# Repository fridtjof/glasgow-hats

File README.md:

# some HATs for the glasgow

okay there's just one so far but i've got another one i just haven't
put together yet. it's pretty simple, too.

## kicad library

in the 'kicadlib' directory, and the Releases area of github, there's
a downloadable library you can install into kicad which includes two
symbols and a footprint for making glasgow HATs. see the README in that
directory for more details.

## super breakout screw terminal hat

the name could use some work. brings the pins multiple ways, ending
in screw terminals with some holes through the PCB for optional
strain relief.

this was created when i was working on interfacing with something
through a cable i'd cut in half. i needed to bring the individual
wires into screw terminals, ideally keeping them from pulling out.
i also had to put a logic analyzer and a scope on some of the lines
to figure out what was going on. this would've been really handy.

# related content

- [my glasgow fork](https://github.com/jkominek/glasgow) has the various
  applets i've written, in it.
- [x16glasgow](https://github.com/jkominek/x16glasgow) is a HAT which adapts
  the glasgow to the Commander X16's bus as an MMIO device.

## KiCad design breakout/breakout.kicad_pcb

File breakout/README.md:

# features

Okay, per the picture:

you can work out most things.

The four rows of 0.100" header pins are intended to go female, male,
male, female, to minimize the opportunity for shorts with the female
header that the board uses to plug into the glasgow.

Speaking of which, if you used a header with very long pins for that,
you could plug the breakout cable that comes with the 1BitSquared
Glasgow into those pins, and use it, too.

The 8-pin connector is intended for looped test points, so that you
can clip oscilloscope probes on to the lines. The exposed planes along
the edges are for your probe's ground clip.

On the right there's space for screw terminals. Ground is
available twice, just in case there are two grounds in the cable
(or whatever) that you're working with, and you'd like to secure
both of them.

Finally, the little holes are for optional strain relief. You can run
your wires through them before tightening them down in the screw
terminals. Should reduce the likelihood that they'll pop out at an
awkward moment.

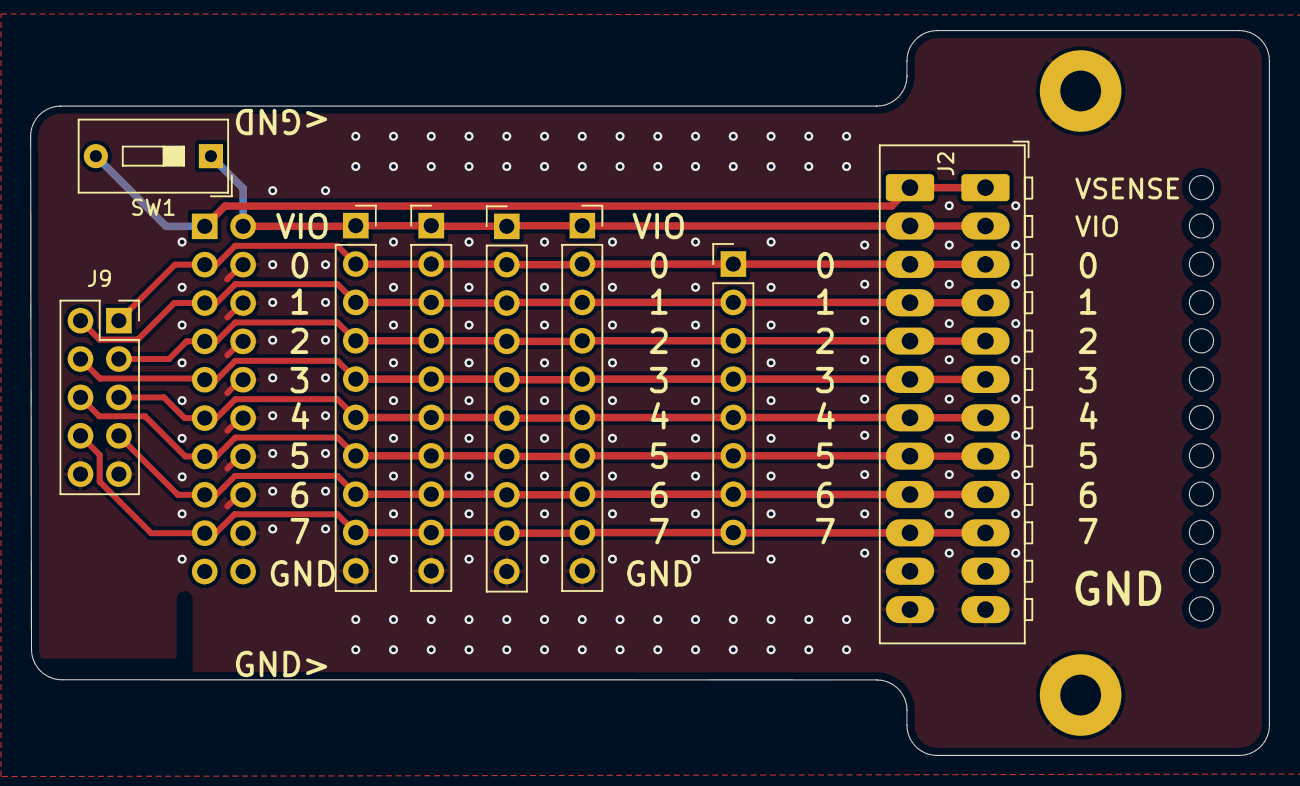
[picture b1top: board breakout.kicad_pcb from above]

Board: 2 copper layers, 82.0 x 48.0 mm, 11 parts (1 on the bottom side), 11 nets.

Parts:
H1, H2: MountingHole_Pad; MountingHole_2.7mm_M2.5_Pad
J1: Glasgow; PinSocket_2x10_P2.54mm_Vertical
J2: ScrewTerminals; TerminalBlock_not_WAGO_233-512_2x12_P2.54mm
J3, J5: SignalsMale; PinHeader_1x10_P2.54mm_Vertical
J4, J6: SignalsFemale; PinSocket_1x10_P2.54mm_Vertical
J7: TestPoints; PinHeader_1x08_P2.54mm_Vertical
J9: FX2LA; PinSocket_2x05_P2.54mm_Vertical
SW1: SW_SPST; SW_DIP_SPSTx01_Slide_9.78x4.72mm_W7.62mm_P2.54mm

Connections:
/D0: J1.3, J2.3, J3.2, J4.2, J5.2, J6.2, J7.1, J9.1
/D1: J1.5, J2.4, J3.3, J4.3, J5.3, J6.3, J7.2, J9.2
/D2: J1.7, J2.5, J3.4, J4.4, J5.4, J6.4, J7.3, J9.3
/D3: J1.9, J2.6, J3.5, J4.5, J5.5, J6.5, J7.4, J9.4
/D4: J1.11, J2.7, J3.6, J4.6, J5.6, J6.6, J7.5, J9.5
/D5: J1.13, J2.8, J3.7, J4.7, J5.7, J6.7, J7.6, J9.6
/D6: J1.15, J2.9, J3.8, J4.8, J5.8, J6.8, J7.7, J9.7
/D7: J1.17, J2.10, J3.9, J4.9, J5.9, J6.9, J7.8, J9.8
/VSENSE: J1.1, J2.1, SW1.2 (B)
GND: H1.1, H2.1, J1.4, J1.6, J1.8, J1.10, J1.12, J1.14, J1.16, J1.18, J2.11, J2.12, J3.10, J4.10, J5.10, J6.10, J9.9, J9.10
VBUS: J1.2, J2.2, J3.1, J4.1, J5.1, J6.1, SW1.1 (A)

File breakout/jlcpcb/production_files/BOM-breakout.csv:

Comment,Designator,Footprint,LCSC
FX2LA,J9,PinSocket_2x05_P2.54mm_Vertical,
SignalsMale,J5,PinHeader_1x10_P2.54mm_Vertical,
SignalsFemale,J4,PinSocket_1x10_P2.54mm_Vertical,
SignalsMale,J3,PinHeader_1x10_P2.54mm_Vertical,
TestPoints,J7,PinHeader_1x08_P2.54mm_Vertical,
ScrewTerminals,J2,TerminalBlock_not_WAGO_233-512_2x12_P2.54mm,
SignalsFemale,J6,PinSocket_1x10_P2.54mm_Vertical,
Glasgow,J1,PinSocket_2x10_P2.54mm_Vertical,

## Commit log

2024-06-12 first HAT
2024-06-12 how to use a completely passive device
2024-06-22 kicad library for making hats
2024-07-29 [wip] add connector for generic fx2 logic analyzers
2024-08-22 get jlc'd
2024-08-22 finished
2024-09-20 wip? rev2
    - rounded corners
    - more LA space (todo confirm spacing re: glasgow center)
    - vio/vsense connection switch
